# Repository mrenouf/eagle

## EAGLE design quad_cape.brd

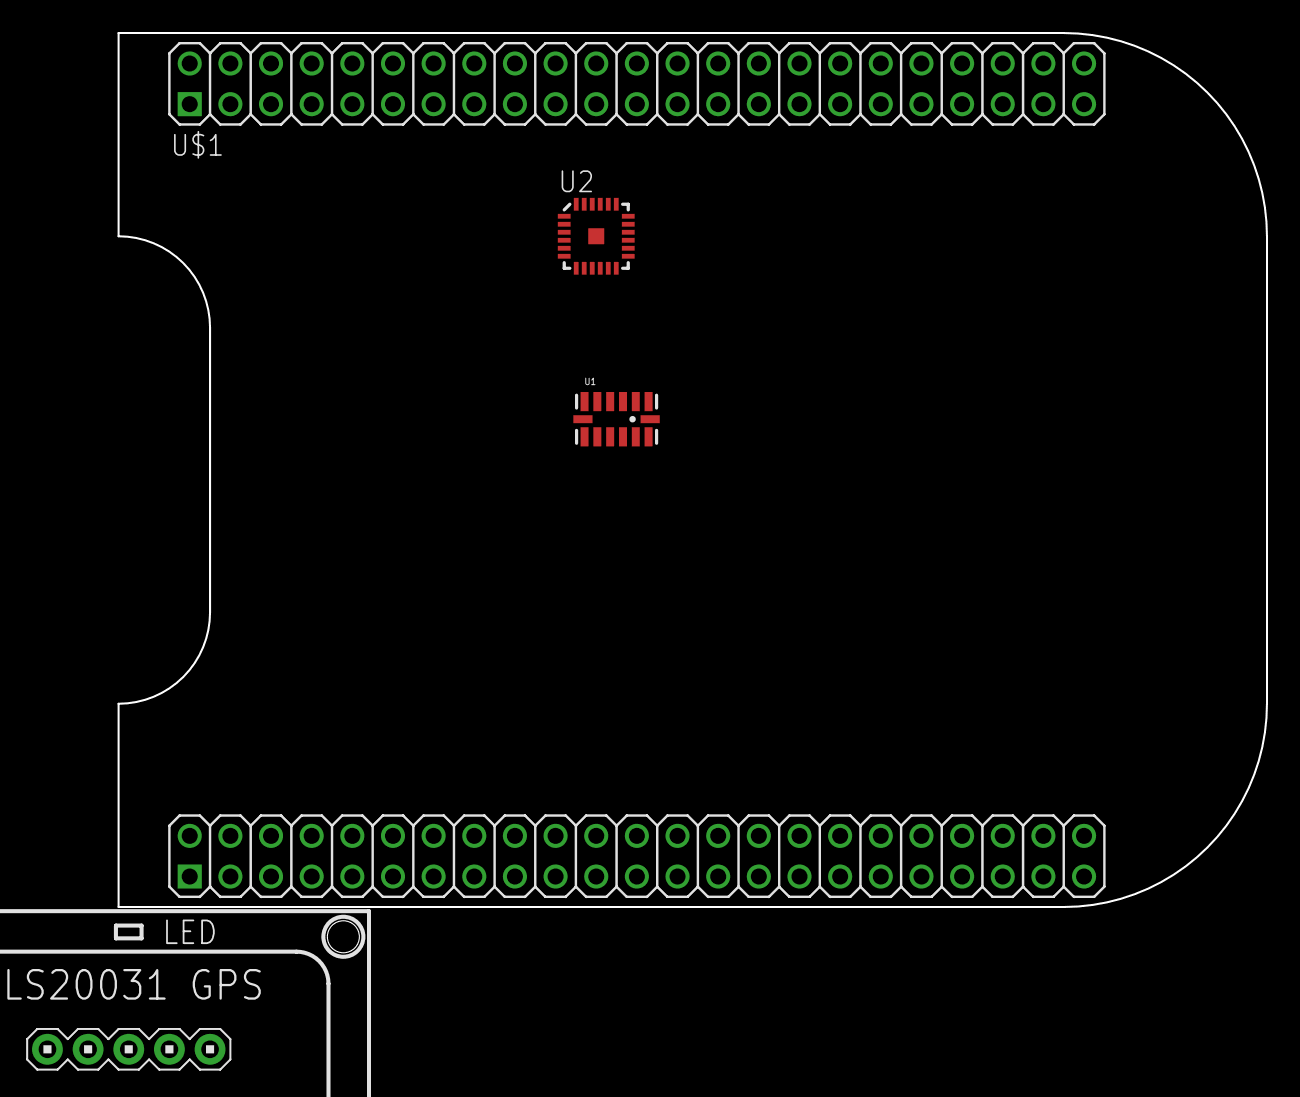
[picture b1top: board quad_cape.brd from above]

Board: 2 copper layers, 71.8 x 54.6 mm, 4 parts (0 on the bottom side), 3 nets, no tracks yet.

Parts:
U1: ADXL345; LGA14
U2: ITG-3200; QFN-24
U3: LS20031
U$1: BEAGLEBONE_OUTLINE; BEAGLEBONE_SHIELD

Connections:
GND: U$1.1, U$1.2, U$1.47, U$1.48
VDD_3V3EXP: U$1.49, U$1.50
VDD_5V: U$1.51, U$1.52

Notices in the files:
parts and their libraries:
SparkFun-Sensors: Licensing: CC v3.0 Share-Alike You are welcome to use this library for commercial purposes.
